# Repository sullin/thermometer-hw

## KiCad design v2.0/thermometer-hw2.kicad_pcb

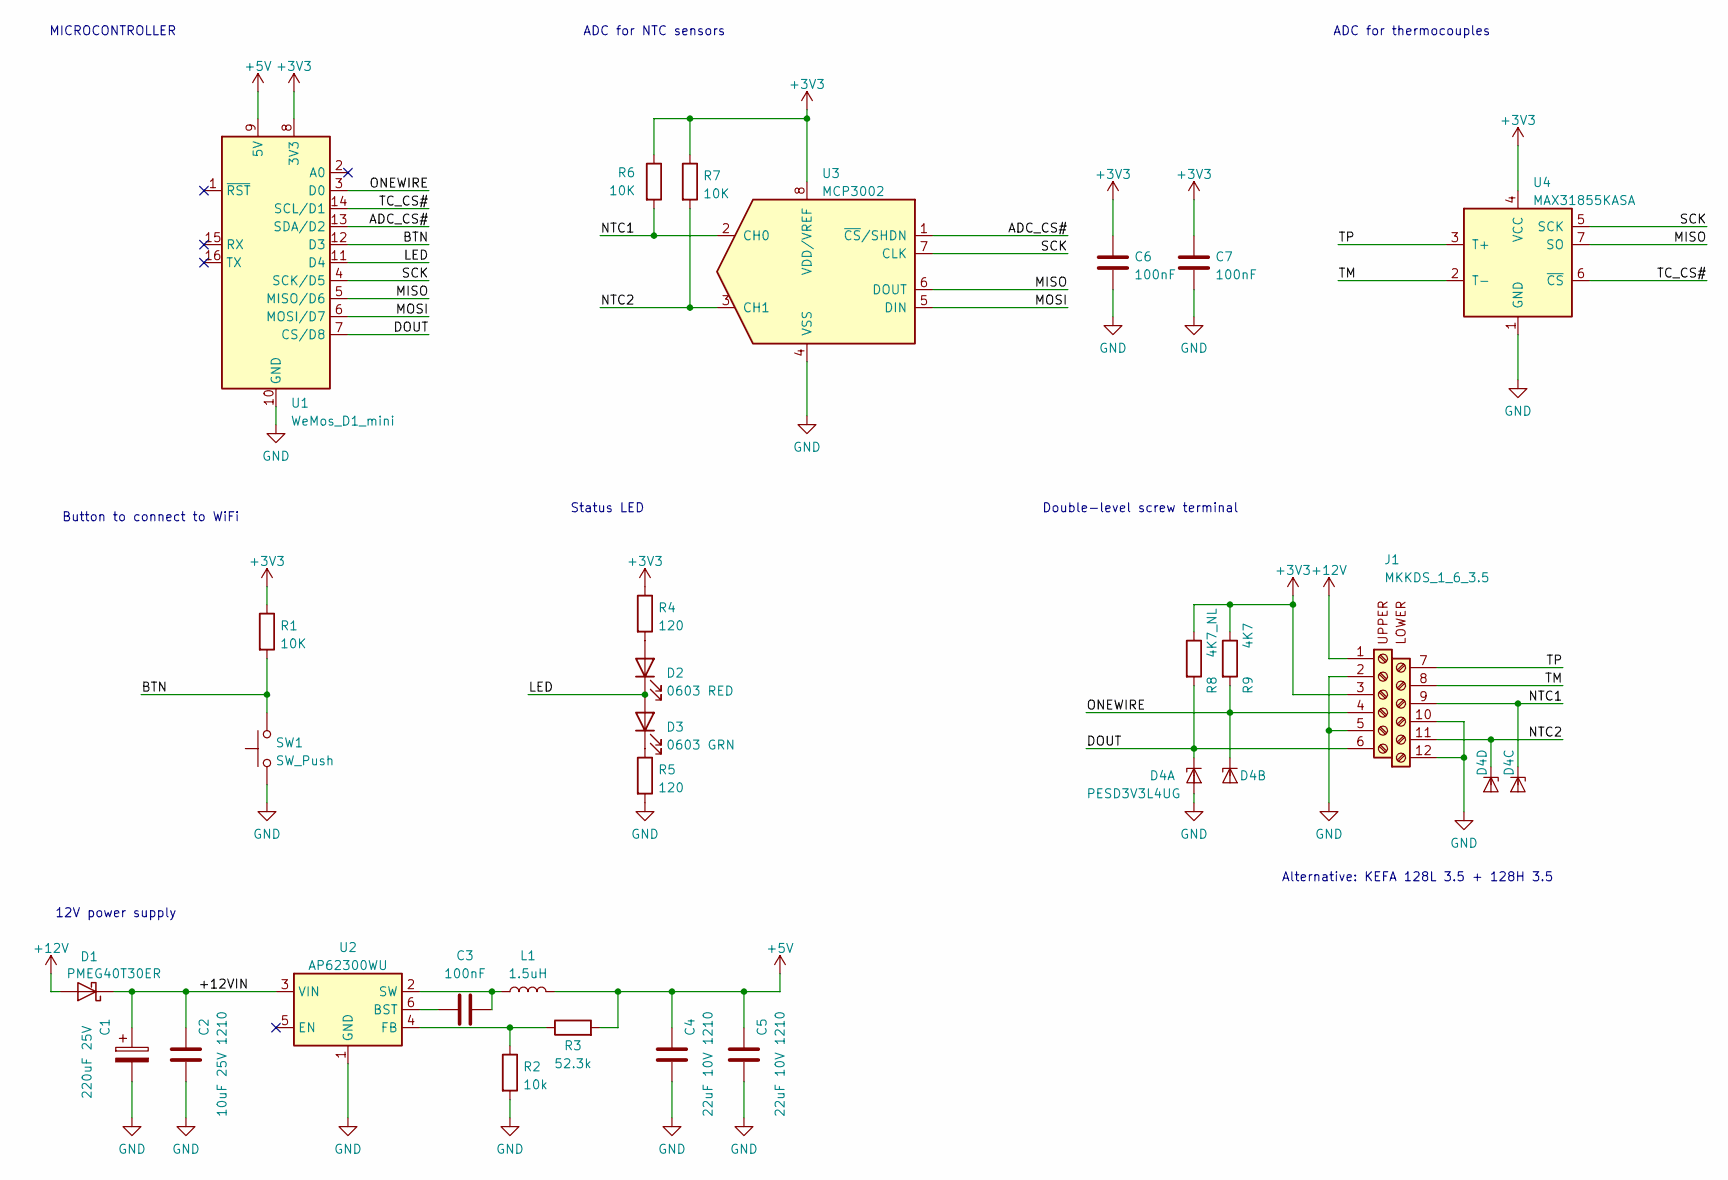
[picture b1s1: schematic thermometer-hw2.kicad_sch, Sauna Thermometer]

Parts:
C1: 220uF 25V; CP_Radial_D8.0mm_P3.50mm
C2: 10uF 25V 1210; C_0805_2012Metric_Pad1.18x1.45mm_HandSolder
C3, C6, C7: 100nF; C_0805_2012Metric_Pad1.18x1.45mm_HandSolder
C4, C5: 22uF 10V 1210; C_0805_2012Metric_Pad1.18x1.45mm_HandSolder
D1: PMEG40T30ER; Nexperia_CFP3_SOD-123W
D2: 0603 RED; LED_0805_2012Metric_Pad1.15x1.40mm_HandSolder
D3: 0603 GRN; LED_0805_2012Metric_Pad1.15x1.40mm_HandSolder
D4: PESD3V3L4UG; SOT-353_SC-70-5
J1: MKKDS_1_6_3.5; PHO_MKKDS_1_6_3.5
L1: 1.5uH; L_1008_2520Metric_Pad1.43x2.20mm_HandSolder
R1, R6, R7: 10K; R_0805_2012Metric_Pad1.20x1.40mm_HandSolder
R2: 10k; R_0805_2012Metric_Pad1.20x1.40mm_HandSolder
R3: 52.3k; R_0805_2012Metric_Pad1.20x1.40mm_HandSolder
R4, R5: 120; R_0805_2012Metric_Pad1.20x1.40mm_HandSolder
R8: 4K7_NL; R_0805_2012Metric_Pad1.20x1.40mm_HandSolder
R9: 4K7; R_0805_2012Metric_Pad1.20x1.40mm_HandSolder
SW1: SW_Push; SW_Tactile_SPST_Angled_PTS645Vx31-2LFS
U1: WeMos_D1_mini; WEMOS_D1_mini_light_flip
U2: AP62300WU; TSOT-23-6
U3: MCP3002; SOIC-8_3.9x4.9mm_P1.27mm
U4: MAX31855KASA; SOIC-8_3.9x4.9mm_P1.27mm

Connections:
+3V3: C6.1, C7.1, J1.3, R1.1, R4.1, R6.1, R7.1, R8.1, R9.1, U1.8 (3V3), U3.8 (VDD/VREF), U4.4 (VCC)
+5V: C4.1, C5.1, L1.2, R3.2, U1.9 (5V)
+12V: D1.2 (A), J1.1
/+12VIN: C1.1, C2.1, D1.1 (K), U2.3 (VIN)
/ADC_CS#: U1.13 (SDA/D2), U3.1 (~CS/SHDN)
/BTN: R1.2, SW1.2, U1.12 (D3)
/DOUT: D4.1 (K1), J1.6, R8.2, U1.7 (CS/D8)
/LED: D2.1 (K), D3.2 (A), U1.11 (D4)
/MISO: U1.5 (MISO/D6), U3.6 (DOUT), U4.7 (SO)
/MOSI: U1.6 (MOSI/D7), U3.5 (DIN)
/NTC1: D4.4 (K3), J1.9, R6.2, U3.2 (CH0)
/NTC2: D4.5 (K4), J1.11, R7.2, U3.3 (CH1)
/ONEWIRE: D4.3 (K2), J1.4, R9.2, U1.3 (D0)
/SCK: U1.4 (SCK/D5), U3.7 (CLK), U4.5 (SCK)
/TC_CS#: U1.14 (SCL/D1), U4.6 (~CS)
/TM: J1.8, U4.2 (T-)
/TP: J1.7, U4.3 (T+)
GND: C1.2, C2.2, C4.2, C5.2, C6.2, C7.2, D4.2 (A), J1.2, J1.5, J1.10, J1.12, R2.2, R5.2, SW1.1, U1.10 (GND), U2.1 (GND), U3.4 (VSS), U4.1 (GND)
unnamed: C3.1, U2.6 (BST)
unnamed: C3.2, L1.1, U2.2 (SW)
unnamed: D2.2 (A), R4.2
unnamed: D3.1 (K), R5.1
unnamed: R2.1, R3.1, U2.4 (FB)

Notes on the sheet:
Button to connect to WiFi
MICROCONTROLLER
12V power supply
Status LED
ADC for NTC sensors
Double-level screw terminal
ADC for thermocouples
Alternative: KEFA 128L 3.5 + 128H 3.5

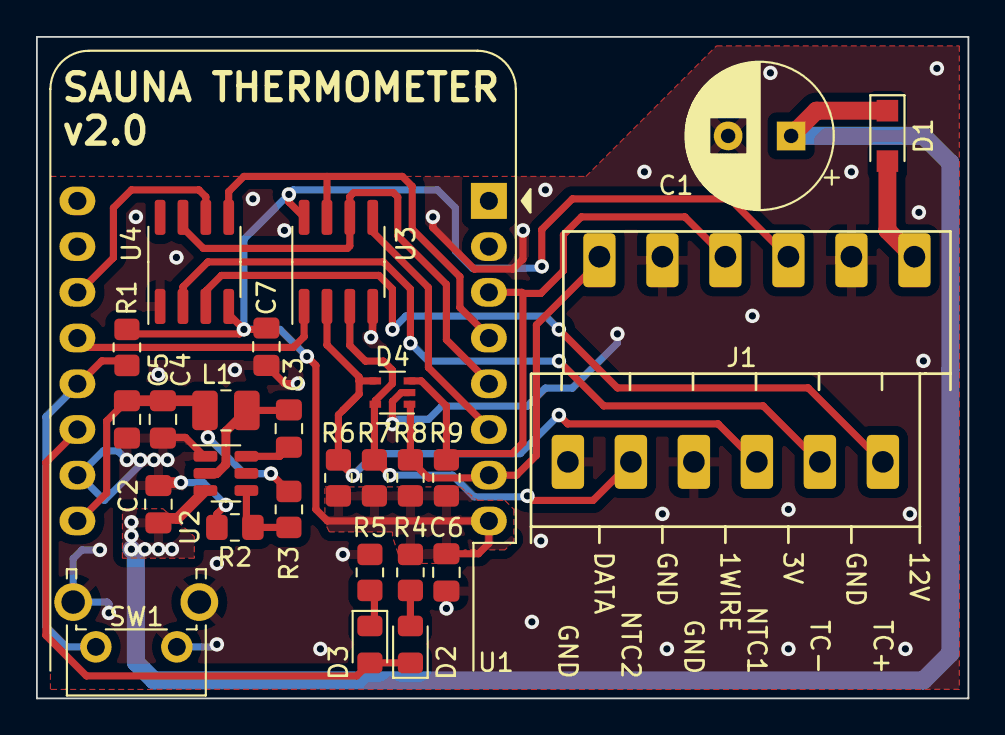
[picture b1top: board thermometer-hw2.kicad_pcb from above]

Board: 2 copper layers, 51.8 x 36.8 mm, 27 parts (0 on the bottom side), 23 nets.

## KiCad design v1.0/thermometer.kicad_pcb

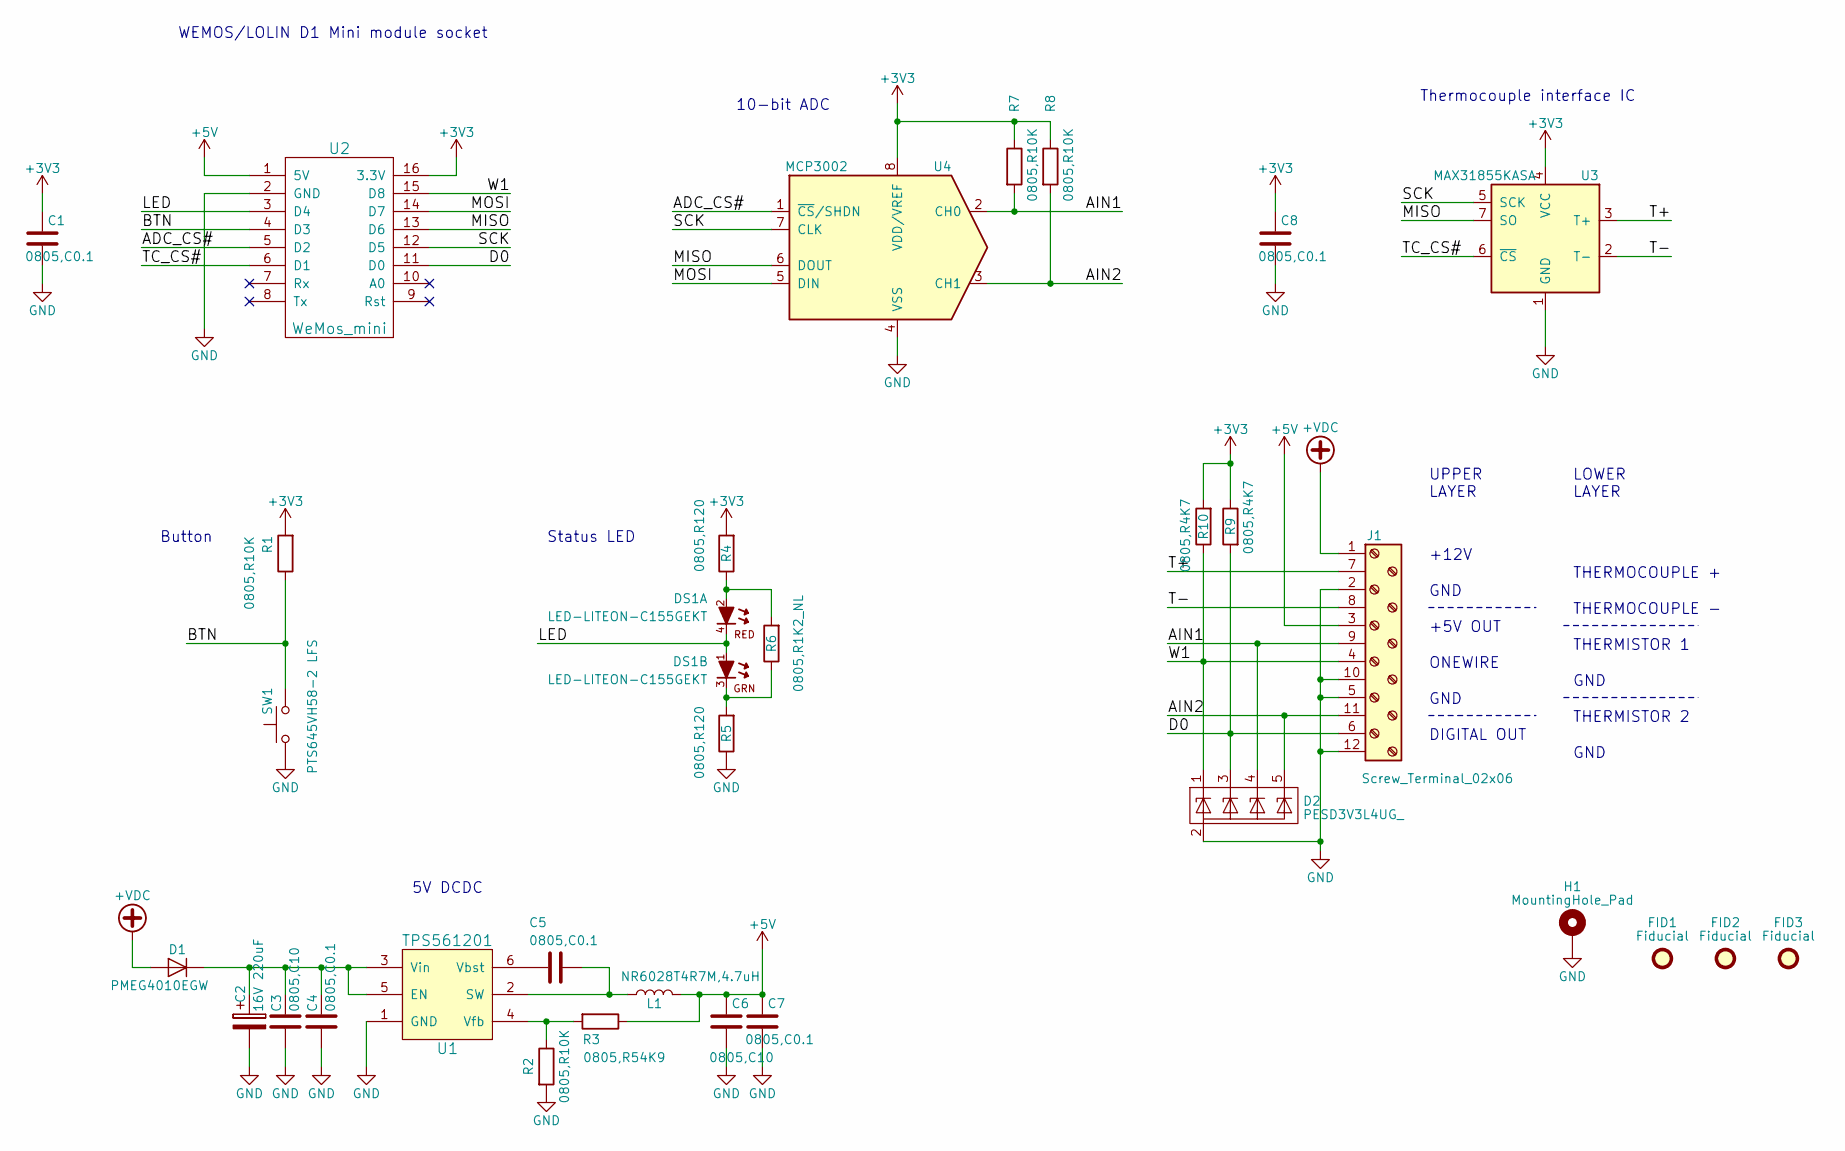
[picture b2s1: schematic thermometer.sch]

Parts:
C1, C4, C5, C7, C8: 0805,C0.1; C_0805
C2: 16V 220uF; CP_Radial_D6.3mm_P2.50mm
C3, C6: 0805,C10; C_0805
D1: PMEG4010EGW; D_SOD-123
D2: PESD3V3L4UG_; SOT-353_SC-70-5_Handsoldering
DS1: LED-LITEON-C155GEKT; LITEON-LED2-C155GEKT
FID1, FID2, FID3: Fiducial; Fiducial_1mm_Mask2mm
H1: MountingHole_Pad; MountingHole_3.2mm_M3_DIN965_Pad
J1: Screw_Terminal_02x06; PHO_MKKDS_1_12-3,5
L1: NR6028T4R7M,4.7uH; L_6.3x6.3_H3
R1, R2, R7, R8: 0805,R10K; R_0805
R3: 0805,R54K9; R_0805
R4, R5: 0805,R120; R_0805
R6: 0805,R1K2_NL; R_0805
R9, R10: 0805,R4K7; R_0805
SW1: PTS645VH58-2 LFS; SW_Tactile_SPST_Angled_PTS645Vx58-2LFS
U1: TPS561201; SOT-23-6
U2: WeMos_mini; D1_mini_board
U3: MAX31855KASA; SOIC-8_3.9x4.9mm_Pitch1.27mm
U4: MCP3002; SOIC-8_3.9x4.9mm_Pitch1.27mm

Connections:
+3V3: C1.1, C8.1, R1.2, R4.2, R7.1, R8.1, R9.1, R10.2, U2.16 (3.3V), U3.4 (VCC), U4.8 (VDD/VREF)
+5V: C6.1, C7.1, J1.3, L1.2, R3.1, U2.1 (5V)
+VDC: D1.2 (A), J1.1
/ADC_CS#: U2.5 (D2), U4.1 (~CS~/SHDN)
/AIN1: D2.4 (K3), J1.9, R7.2, U4.2 (CH0)
/AIN2: D2.5 (K4), J1.11, R8.2, U4.3 (CH1)
/BTN: R1.1, SW1.2, U2.4 (D3)
/D0: D2.3 (K2), J1.6, R9.2, U2.11 (D0)
/LED: DS1.1 (A), DS1.4 (K), U2.3 (D4)
/MISO: U2.13 (D6), U3.7 (SO), U4.6 (DOUT)
/MOSI: U2.14 (D7), U4.5 (DIN)
/SCK: U2.12 (D5), U3.5 (SCK), U4.7 (CLK)
/T+: J1.7, U3.3 (T+)
/T-: J1.8, U3.2 (T-)
/TC_CS#: U2.6 (D1), U3.6 (~CS~)
/W1: D2.1 (K1), J1.4, R10.1, U2.15 (D8)
GND: C1.2, C2.2, C3.2, C4.2, C6.2, C7.2, C8.2, D2.2 (A), H1.1, J1.2, J1.5, J1.10, J1.12, R2.2, R5.1, SW1.1, U1.1 (GND), U2.2 (GND), U3.1 (GND), U4.4 (VSS)
unnamed: C2.1, C3.1, C4.1, D1.1 (K), U1.3 (Vin), U1.5 (EN)
unnamed: C5.1, L1.1, U1.2 (SW)
unnamed: C5.2, U1.6 (Vbst)
unnamed: DS1.2 (A), R4.1, R6.2
unnamed: DS1.3 (K), R5.2, R6.1
unnamed: R2.1, R3.2, U1.4 (Vfb)

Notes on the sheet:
5V DCDC
Status LED
+12V
THERMISTOR 1
THERMISTOR 2
THERMOCOUPLE +
GND
ONEWIRE
DIGITAL OUT
+5V OUT
Button
WEMOS/LOLIN D1 Mini module socket
10-bit ADC
Thermocouple interface IC
UPPER LAYER
LOWER LAYER
THERMOCOUPLE -

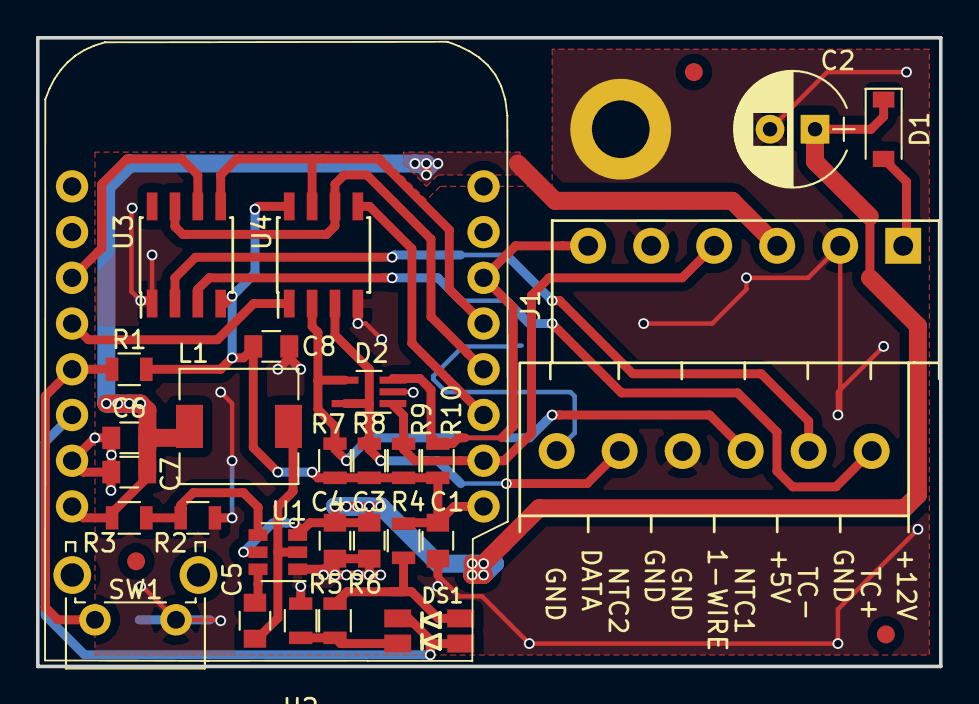
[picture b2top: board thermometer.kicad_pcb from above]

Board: 2 copper layers, 50.2 x 34.9 mm, 32 parts (0 on the bottom side), 23 nets.

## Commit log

2019-03-10 Initial import of v1.0
2019-03-10 add errata
2019-03-10 add 3v3 errata rework drawing
2019-07-20 Add readme
2022-09-06 reorganize git
2022-09-06 add gitignore
2022-09-06 Add v2.0 board
